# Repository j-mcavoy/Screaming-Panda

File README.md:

# Panda Screamer
Open Source Boost Pedal for Guitar and Bass

## Software Used
    * ECAD - KiCad
    * MCAD - FreeCad
    * Graphic Design - Inkscape

## Tutorial
_Coming Soon_

### Bill of Materials
[link]()

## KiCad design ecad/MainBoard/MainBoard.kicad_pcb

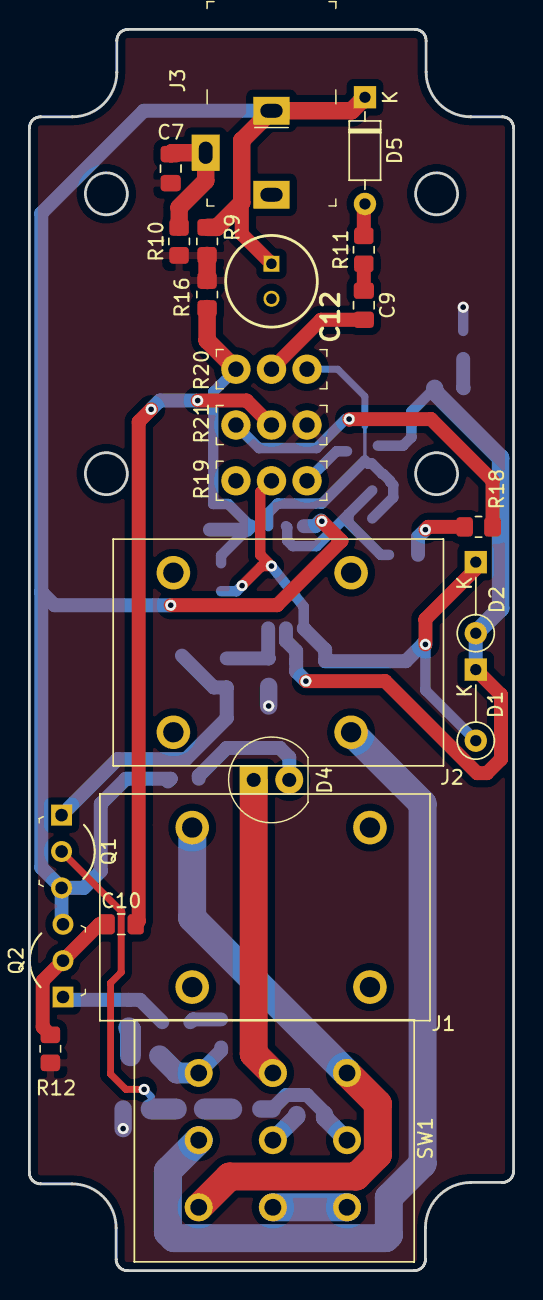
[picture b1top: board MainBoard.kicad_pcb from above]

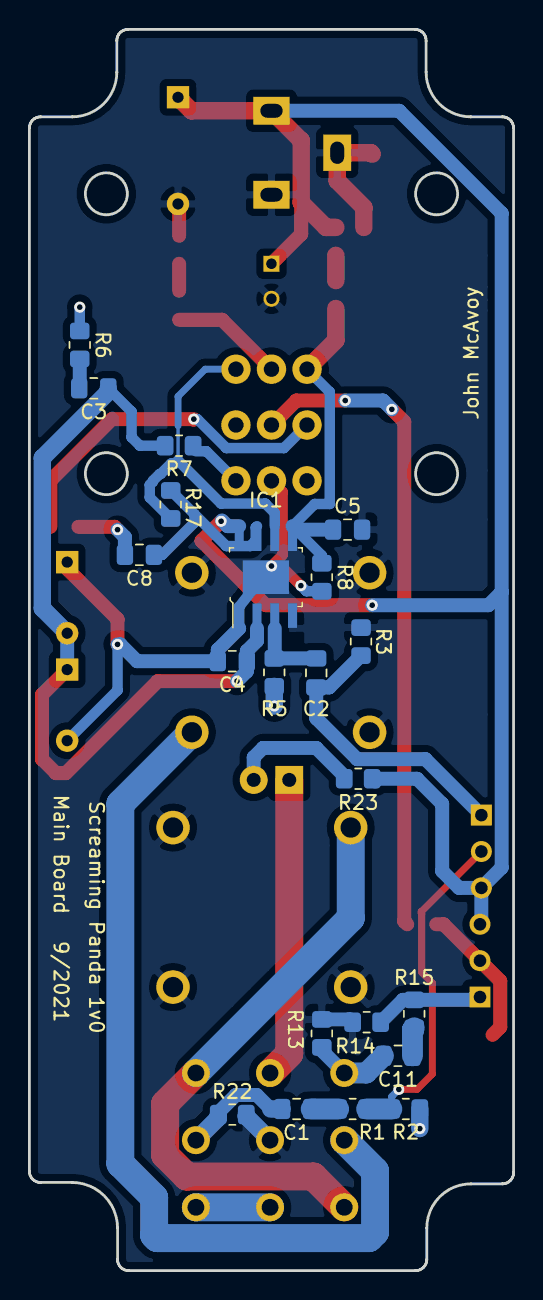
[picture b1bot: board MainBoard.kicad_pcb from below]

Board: 2 copper layers, 34.6 x 88.7 mm, 44 parts (21 on the bottom side), 29 nets.

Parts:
C1: 20n; C_0805_2012Metric_Pad1.18x1.45mm_HandSolder
C2, C8: 1u; C_0805_2012Metric_Pad1.18x1.45mm_HandSolder
C3, C4: 50p; C_0805_2012Metric_Pad1.18x1.45mm_HandSolder
C5, C9: 220n; C_0805_2012Metric_Pad1.18x1.45mm_HandSolder
C7: 47u; C_0805_2012Metric_Pad1.18x1.45mm_HandSolder
C10: 100n; C_0805_2012Metric_Pad1.18x1.45mm_HandSolder
C11: 10u; C_0805_2012Metric_Pad1.18x1.45mm_HandSolder
C12: 100u; CAPPRD250W55D655H1220
D1, D2: 1N914; D_DO-35_SOD27_P5.08mm_Vertical_KathodeUp
D4: LED_BLUE; LED_5mm_Radial
D5: 1N914; D_DO-35_SOD27_P7.62mm_Horizontal
IC1: RC4558; SOIC-8-1EP_W3.9mm
J1, J2: ACJM-HHDR
J3: PJ-102A; Barrel_Jack_5.5mmODx2.1mmID_PJ-102A
Q1, Q2: 2N4424; TO-92-3_Formed_Leads
R1, R8, R17, R18, R23: 1k; R_0805_2012Metric_Pad1.20x1.40mm_HandSolder
R2: 505k; R_0805_2012Metric_Pad1.20x1.40mm_HandSolder
R3, R5, R9, R10, R13, R14, R16: 10k; R_0805_2012Metric_Pad1.20x1.40mm_HandSolder
R6: 4k7; R_0805_2012Metric_Pad1.20x1.40mm_HandSolder
R7: 51k; R_0805_2012Metric_Pad1.20x1.40mm_HandSolder
R11: 220; R_0805_2012Metric_Pad1.20x1.40mm_HandSolder
R12: 510k; R_0805_2012Metric_Pad1.20x1.40mm_HandSolder
R15: 100; R_0805_2012Metric_Pad1.20x1.40mm_HandSolder
R19: 500ka; 75160-195-03LF
R20: 20kb; 75160-195-03LF
R21: 20ka; 75160-195-03LF
R22: 1M5; R_0805_2012Metric_Pad1.20x1.40mm_HandSolder
SW1: FS57003PLT2B2M2QE; SW_PUSH_E-Switch_FS57003PLT_3PDT

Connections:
0: C5.2, C7.2, C12.2, D5.2 (A), IC1.4 (V-), J1.S, J1.SN, J1.TN, J2.S, J2.SN, J2.TN, J3.1, J3.3, R3.2, R10.2, R11.2, R13.2, R14.2, R22.2, SW1.5
+9V: C12.1, D5.1 (K), IC1.8 (V+), J3.2, Q1.3 (C), Q2.3 (C), R9.1, R23.1
/EFFECT_OUT: C11.2, R13.1, SW1.7
/PassThru: J1.T, SW1.1, SW1.9
/SIG_IN: C1.2, R22.1, SW1.2
/SIG_OUT: J2.T, SW1.8
/drive/IN: C2.1, Q1.1 (E), R3.1
/drive/OUT: C5.1, IC1.5 (+), R8.1, R16.2, R20.1
/tone/OUT: C8.1, IC1.7, R17.1
unnamed: C1.1, R1.2
unnamed: C2.2, IC1.3 (+), R5.2
unnamed: C3.1, C4.1, D1.1 (K), D2.2 (A), IC1.2 (-), R7.2
unnamed: C3.2, R6.2
unnamed: C4.2, D1.2 (A), D2.1 (K), IC1.1, R8.2, R19.2
unnamed: C8.2, R18.2
unnamed: C9.1, R11.1
unnamed: C9.2, R20.2
unnamed: C10.1, Q2.2 (B), R12.2
unnamed: C10.2, R21.2
unnamed: C11.1, R15.1
unnamed: D4.1 (K), SW1.4
unnamed: D4.2 (A), R23.2
unnamed: IC1.6 (-), R17.2, R20.3
unnamed: Q1.2 (B), R1.1, R2.2
unnamed: Q2.1 (E), R14.1, R15.2
unnamed: R18.1, R21.1
unnamed: R7.1, R19.3
unnamed: SW1.3, SW1.6
VCC: C7.1, R2.1, R5.1, R6.1, R9.2, R10.1, R12.1, R16.1, R21.3

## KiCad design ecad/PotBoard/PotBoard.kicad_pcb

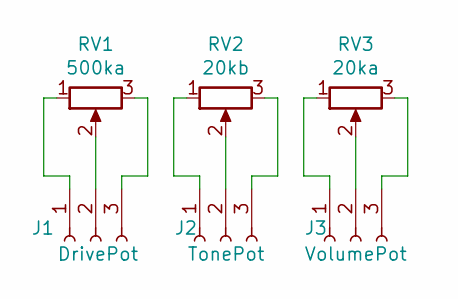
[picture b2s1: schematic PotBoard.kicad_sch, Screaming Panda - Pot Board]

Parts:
J1: DrivePot; C031LFBN-RC; MPN C031LFBN-RC
J2: TonePot; C031LFBN-RC; MPN C031LFBN-RC
J3: VolumePot; C031LFBN-RC; MPN C031LFBN-RC
RV1: 500ka; Potentiometer_Bourns_PTV09A-1_Single_Vertical; MPN PTV09A-4020F-A504
RV2: 20kb; Potentiometer_Bourns_PTV09A-1_Single_Vertical; MPN PTV09A-4020F-B203
RV3: 20ka; Potentiometer_Bourns_PTV09A-1_Single_Vertical; MPN PTV09A-4020F-A203

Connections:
unnamed: J1.1, RV1.1
unnamed: J1.2, RV1.2
unnamed: J1.3, RV1.3
unnamed: J2.1, RV2.1
unnamed: J2.2, RV2.2
unnamed: J2.3, RV2.3
unnamed: J3.1, RV3.1
unnamed: J3.2, RV3.2
unnamed: J3.3, RV3.3

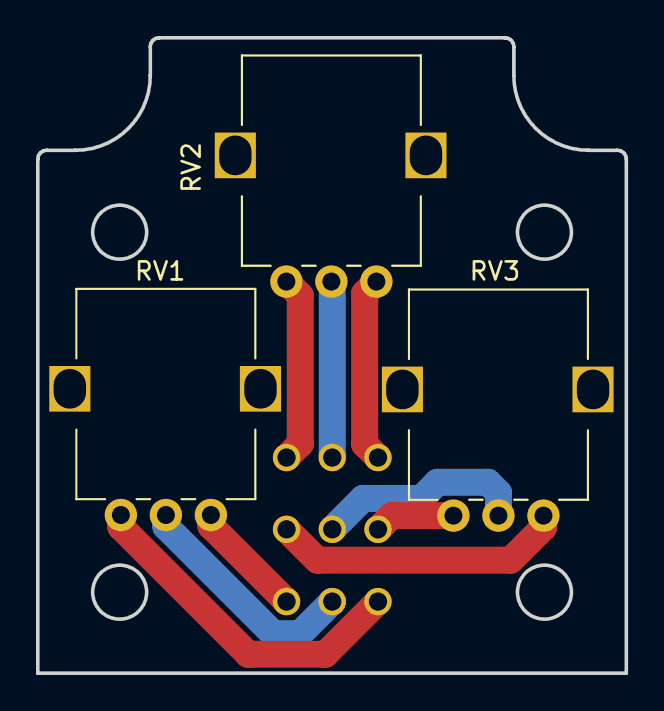
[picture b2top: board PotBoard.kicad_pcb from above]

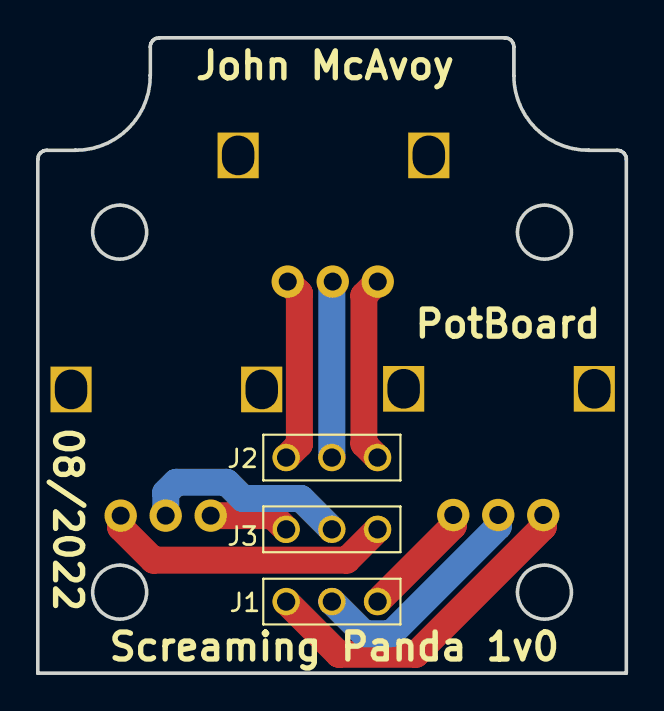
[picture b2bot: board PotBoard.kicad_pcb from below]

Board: 2 copper layers, 32.7 x 35.3 mm, 6 parts (3 on the bottom side), 9 nets.

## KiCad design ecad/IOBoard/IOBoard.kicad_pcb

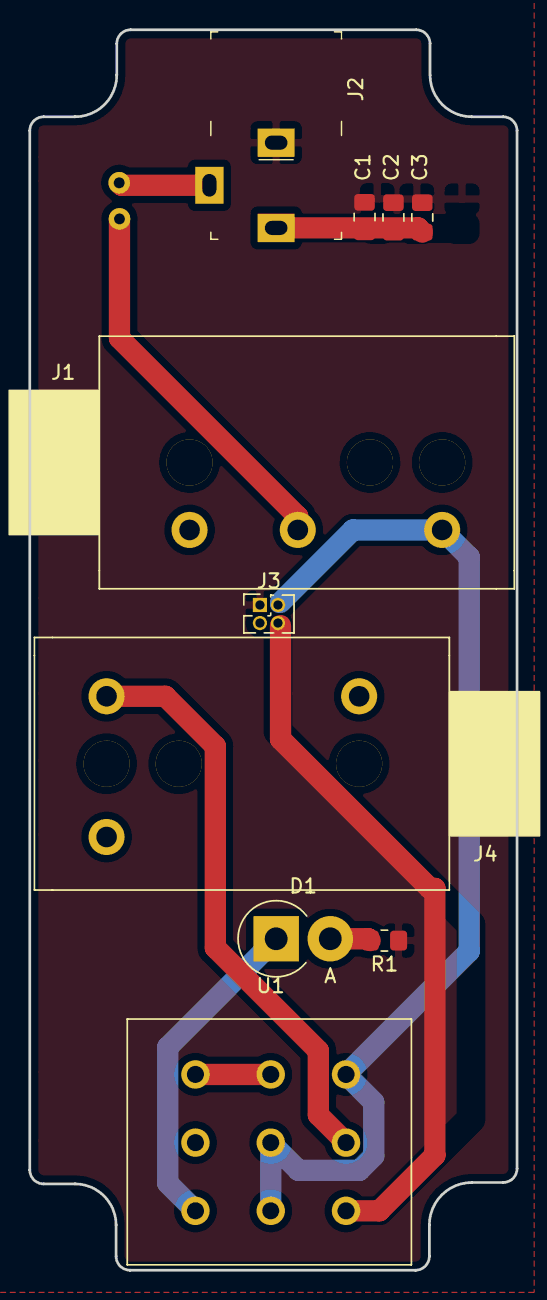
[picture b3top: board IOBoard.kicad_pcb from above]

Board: 2 copper layers, 34.3 x 87.3 mm, 11 parts (1 on the bottom side), 10 nets.

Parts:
BAT1: BC9VPC; PinHeader_1x2_P2.54mm
C1: 100u; C_0805_2012Metric_Pad1.18x1.45mm_HandSolder
C2: 1u; C_0805_2012Metric_Pad1.18x1.45mm_HandSolder
C3: 10n; C_0805_2012Metric_Pad1.18x1.45mm_HandSolder
D1: LED; D_DO-201AD_P3.81mm_Vertical_AnodeUp
J1: SN37A12B; Switchcraft_SN37A12B
J2: PJ-102A; Barrel_Jack_5.5mmODx2.1mmID_PJ-102A
J3: toEffectsBoard; PinHeader_2x02_P1.27mm_Vertical
J4: SN37A12A; Switchcraft_SN37A12A
R1: 1k; R_0805_2012Metric_Pad1.20x1.40mm_HandSolder
U1: FS57003PLT2B2M2QE; SW_PUSH_E-Switch_FS57003PLT_3PDT

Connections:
+9V: C1.1, C2.1, C3.1, J2.2, J3.1, R1.1
/EFFECT_OUT: J3.4, U1.7
/SIG_IN: J1.T, J3.2, U1.4, U1.5, U1.9
/SIG_OUT: J4.T, U1.8
GND: C1.2, C2.2, C3.2, J1.S, J2.1, J3.3, J4.S, J4.TB, U1.2
unnamed: BAT1.NEG, J1.R
unnamed: BAT1.POS, J2.3
unnamed: D1.1, U1.1
unnamed: D1.2, R1.2
unnamed: U1.3, U1.6

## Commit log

2020-04-09 Add mcad
2020-04-09 Update gitignore
2020-04-09 ignore _*
2020-05-28 Add README.md
2020-05-28 Add LISENCE
2020-05-28 Merge
2020-05-28 Migrate to Tube Screamer circuit
2020-05-29 Add Effects Board schematic
2020-05-30 Add PCB layouts
2020-05-30 Update lib
2020-05-30 Add Panda Screamer inital clearence
2020-06-04 Push before switch to PCB connector
2021-01-15 Remove old files
2021-01-17 Renamed: screaming_panda_icon.svg.2020_08_18_14_23_14.0.svg -> enclosure_outline.svg
2021-01-17 Remove IOBoard files
2021-01-17 Add schematic.pdf
2021-01-17 Add IOBoard
2021-01-18 Add rev 1.0 EffectsBoard and IOBoard
2021-01-20 Update IOBoard
2021-01-22 Update bom
2021-01-22 Update libraries and CAD
2021-01-22 Add base board outlines and enslosure cad
2021-01-23 Add booard outline
2021-01-23 Route IOBoard
2021-01-23 Add barrel jack 3D step
2021-01-24 Add QBL8XX60D model
2021-01-24 Add barrel jack to library
2021-01-24 Add LED datasheet
2021-01-24 Move datasheets to root
2021-01-24 Schematic alignment
2021-01-24 Rearrange schematics
2021-01-24 Fix annotation
2021-01-26 Add step_imports
2021-01-26 Add board outlines and references
2021-01-26 Update ecad autosave
2021-01-26 Remove FreeCAD models
2021-01-28 Update before switch to single-board design
2021-01-31 Rename to MainBoard - PotBoard
2021-08-03 Update .gitlab-ci.yml file
2021-08-03 Big commit
    Spice Simulations
    Finalize ECAD schematic
    old MCAD stuff
2021-08-07 Update BOM and SPIRCE SIM
    Add netlist to calculate power dissipation through each resistor
2021-08-08 Corrections + SPICE Model Finally fixed :)
2021-08-12 Clean up
    Remove old mcad files
    Add onshap.url
2021-08-13 Clean up ecad
2021-08-17 Update ecad BOM
    Change transistor to 2N4424
2021-08-17 Add octopart BOM link
2021-08-31 Update layouts with finished mcad
2021-09-14 Update mcad step's and drawings
2021-09-14 Update ecad lib
2021-09-20 Library recovery
2021-09-20 PCB layout after data loss
2021-09-20 Layout all components, first revision
2021-09-20 Fix DRC issues
2021-09-20 Move references
2021-10-05 Board 1v0
2021-10-17 Change to using kicad-library submodule
2022-02-06 Fix submodule path
2022-02-06 Remove j-mcavoy kicad lib submodule
2022-02-06 Fix gitignore merge
2022-02-06 Update libraries to j-mcavoy kicad library
2022-02-07 Add kibot.yml
2022-02-07 try github workflows
